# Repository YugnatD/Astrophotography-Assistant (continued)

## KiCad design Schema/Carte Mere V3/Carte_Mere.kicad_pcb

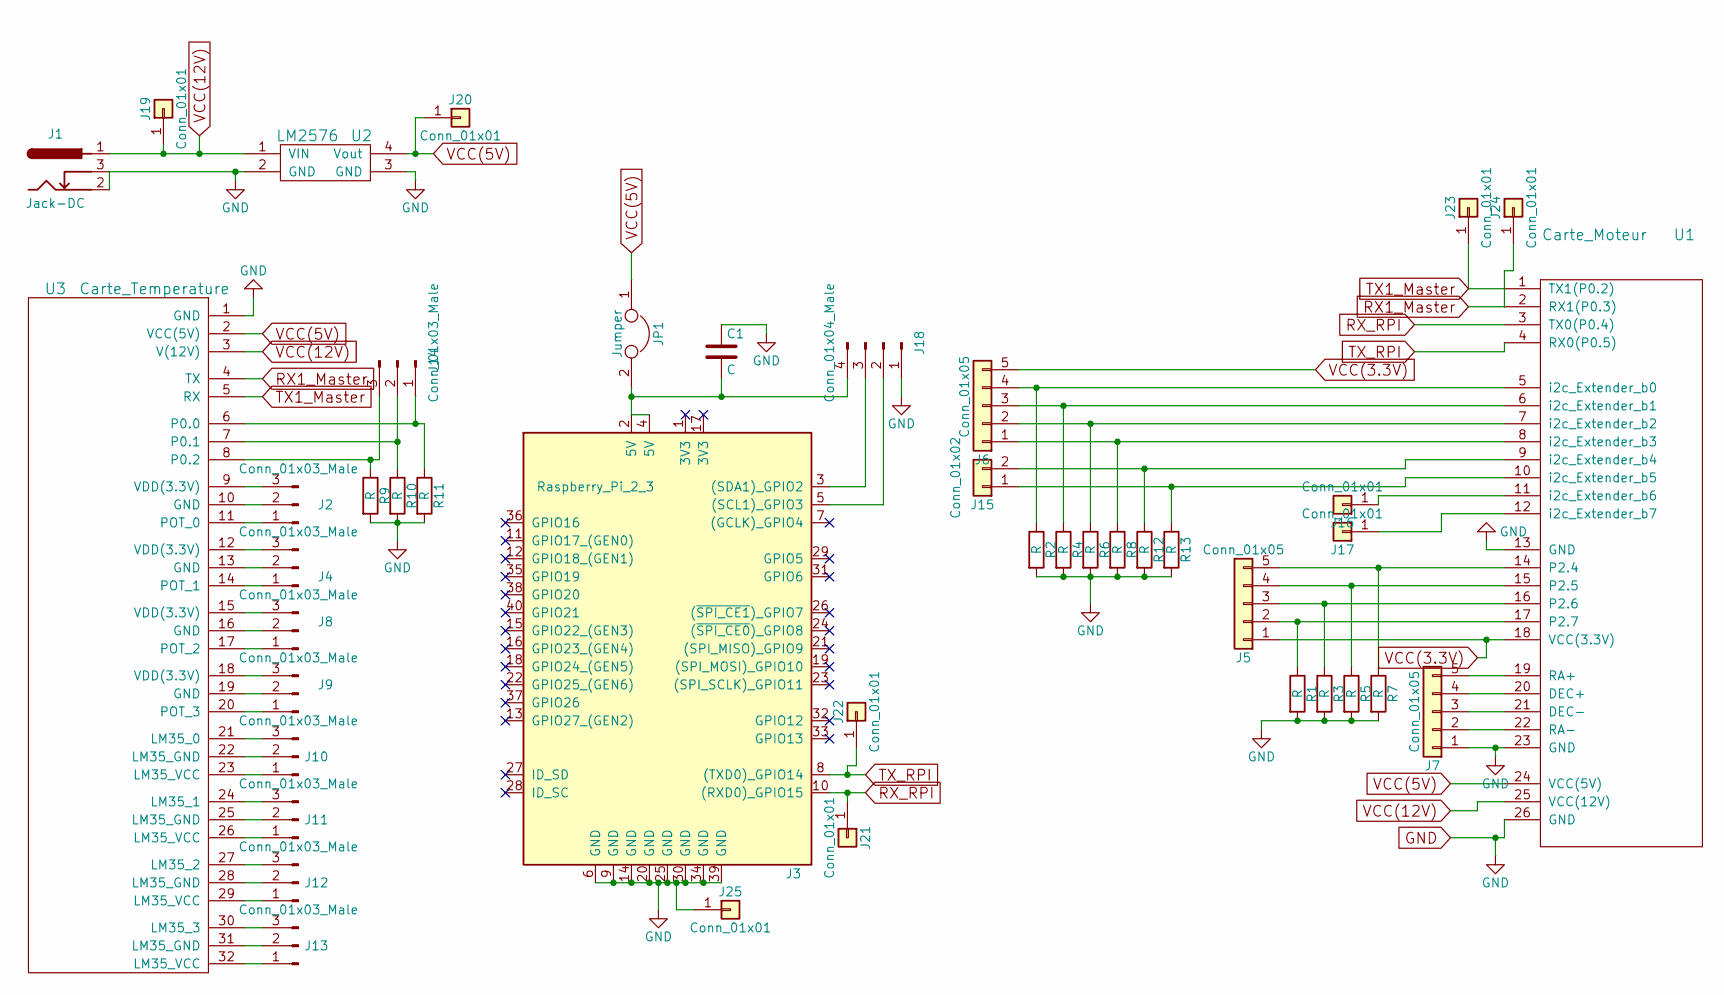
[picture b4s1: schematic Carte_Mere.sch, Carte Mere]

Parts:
C1: C; CP_Radial_D5.0mm_P2.00mm
J1: Jack-DC; JACK_ALIM
J2, J4, J8, J9, J10, J11, J12, J13, J14: Conn_01x03_Male; Pin_Header_Straight_1x03_Pitch2.54mm
J3: Raspberry_Pi_2_3; RaspberryPI3_V2
J5, J6, J7: Conn_01x05; Pin_Header_Straight_1x05_Pitch2.54mm
J15: Conn_01x02; Pin_alimentation
J16, J17, J19, J20, J21, J22, J23, J24, J25: Conn_01x01; TSC_CON1_poignard
J18: Conn_01x04_Male; Pin_Header_Straight_1x04_Pitch2.54mm
JP1: Jumper; Pin_alimentation
R1, R2, R3, R4, R5, R6, R7, R8, R9, R10, R11, R12, R13: R; R_1206_HandSoldering
U1: Carte_Moteur; Carte_Moteur_V2
U2: LM2576; Alimentation_V2
U3: Carte_Temperature

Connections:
GND: C1.1, J1.2, J1.3, J3.6 (GND), J3.9 (GND), J3.14 (GND), J3.20 (GND), J3.25 (GND), J3.30 (GND), J3.34 (GND), J3.39 (GND), J7.1, J18.1, J25.1, R1.2, R2.2, R3.2, R4.2, R5.2, R6.2, R7.2, R8.2, R9.2, R10.2, R11.2, R12.2, R13.2, U1.13 (GND), U1.23 (GND), U1.26 (GND), U2.2 (GND), U2.3 (GND), U3.1 (GND)
unnamed: C1.2, J3.2 (5V), J3.4 (5V), J18.4, JP1.2
unnamed: J2.1, U3.11 (POT_0)
unnamed: J2.2, U3.10 (GND)
unnamed: J2.3, U3.9 (VDD(3.3V))
unnamed: J4.1, U3.14 (POT_1)
unnamed: J4.2, U3.13 (GND)
unnamed: J4.3, U3.12 (VDD(3.3V))
unnamed: J5.2, R1.1, U1.17 (P2.7)
unnamed: J5.3, R3.1, U1.16 (P2.6)
unnamed: J5.4, R5.1, U1.15 (P2.5)
unnamed: J5.5, R7.1, U1.14 (P2.4)
unnamed: J6.1, R8.1, U1.8 (i2c_Extender_b3)
unnamed: J6.2, R6.1, U1.7 (i2c_Extender_b2)
unnamed: J6.3, R4.1, U1.6 (i2c_Extender_b1)
unnamed: J6.4, R2.1, U1.5 (i2c_Extender_b0)
unnamed: J7.2, U1.22 (RA-)
unnamed: J7.3, U1.21 (DEC-)
unnamed: J7.4, U1.20 (DEC+)
unnamed: J7.5, U1.19 (RA+)
unnamed: J8.1, U3.17 (POT_2)
unnamed: J8.2, U3.16 (GND)
unnamed: J8.3, U3.15 (VDD(3.3V))
unnamed: J9.1, U3.20 (POT_3)
unnamed: J9.2, U3.19 (GND)
unnamed: J9.3, U3.18 (VDD(3.3V))
unnamed: J10.1, U3.23 (LM35_VCC)
unnamed: J10.2, U3.22 (LM35_GND)
unnamed: J10.3, U3.21 (LM35_0)
unnamed: J11.1, U3.26 (LM35_VCC)
unnamed: J11.2, U3.25 (LM35_GND)
unnamed: J11.3, U3.24 (LM35_1)
unnamed: J12.1, U3.29 (LM35_VCC)
unnamed: J12.2, U3.28 (LM35_GND)
unnamed: J12.3, U3.27 (LM35_2)
unnamed: J13.1, U3.32 (LM35_VCC)
unnamed: J13.2, U3.31 (LM35_GND)
unnamed: J13.3, U3.30 (LM35_3)
unnamed: J14.1, R11.1, U3.6 (P0.0)
unnamed: J14.2, R10.1, U3.7 (P0.1)
unnamed: J14.3, R9.1, U3.8 (P0.2)
unnamed: J15.1, R13.1, U1.10 (i2c_Extender_b5)
unnamed: J15.2, R12.1, U1.9 (i2c_Extender_b4)
unnamed: J16.1, U1.11 (i2c_Extender_b6)
unnamed: J17.1, U1.12 (i2c_Extender_b7)
unnamed: J3.5 ((SCL1)_GPIO3), J18.2
unnamed: J3.3 ((SDA1)_GPIO2), J18.3
RX1_Master: J24.1, U1.2 (RX1(P0.3)), U3.4 (TX)
RX_RPI: J3.10 ((RXD0)_GPIO15), J21.1, U1.3 (TX0(P0.4))
TX1_Master: J23.1, U1.1 (TX1(P0.2)), U3.5 (RX)
TX_RPI: J3.8 ((TXD0)_GPIO14), J22.1, U1.4 (RX0(P0.5))
VCC(3.3V): J5.1, J6.5, U1.18 (VCC(3.3V))
VCC(5V): J20.1, JP1.1, U1.24 (VCC(5V)), U2.4 (Vout), U3.2 (VCC(5V))
VCC(12V): J1.1, J19.1, U1.25 (VCC(12V)), U2.1 (VIN), U3.3 (V(12V))

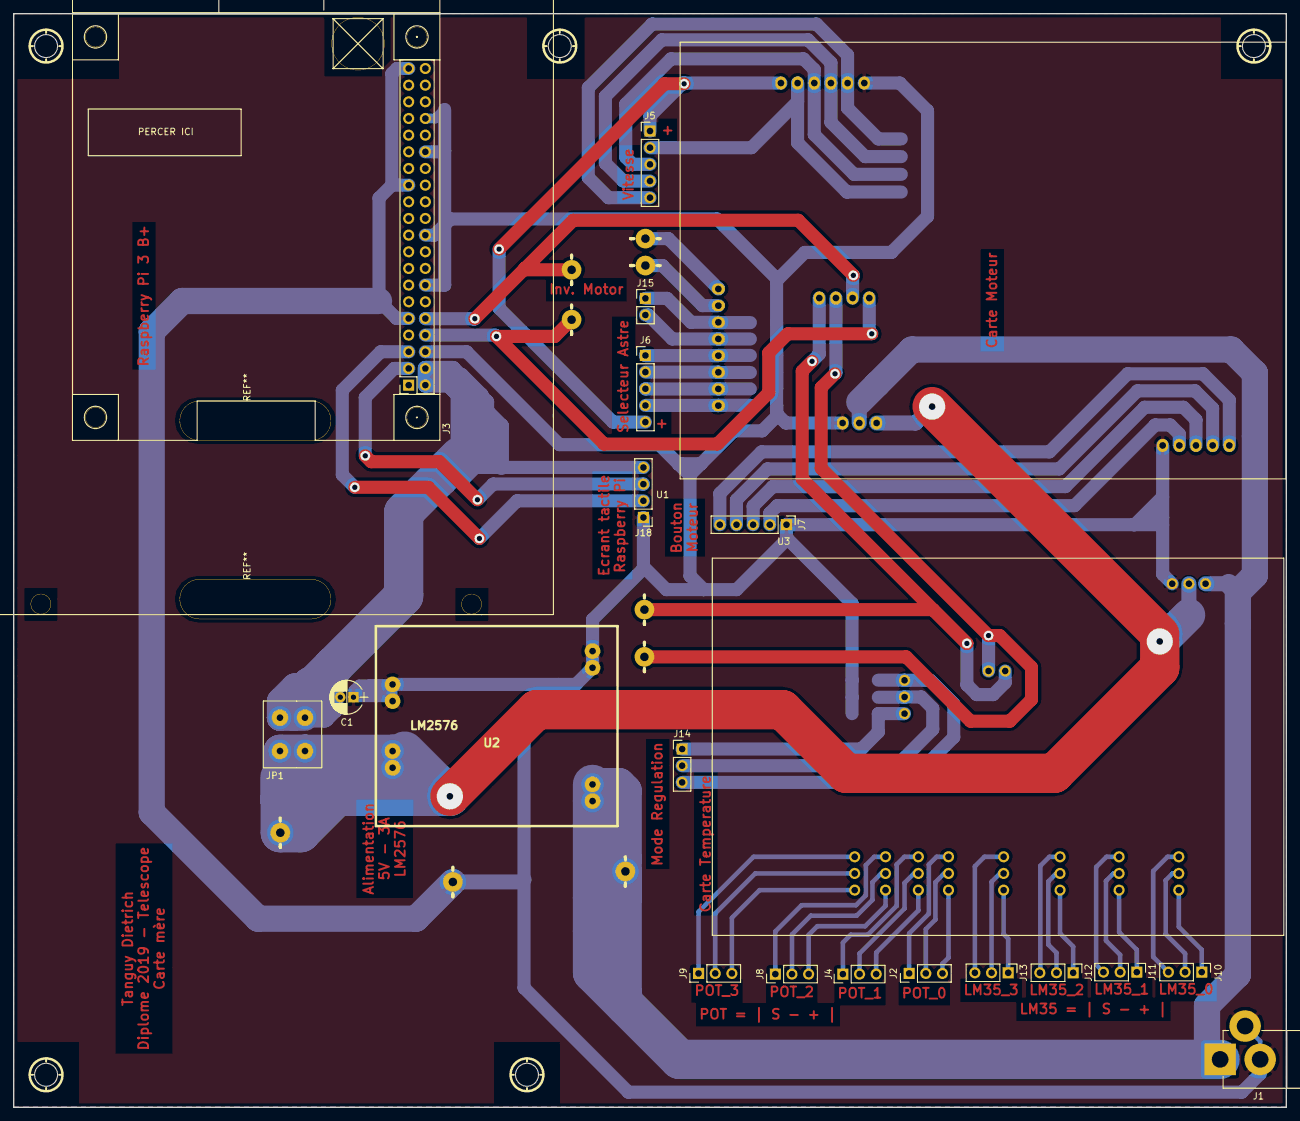
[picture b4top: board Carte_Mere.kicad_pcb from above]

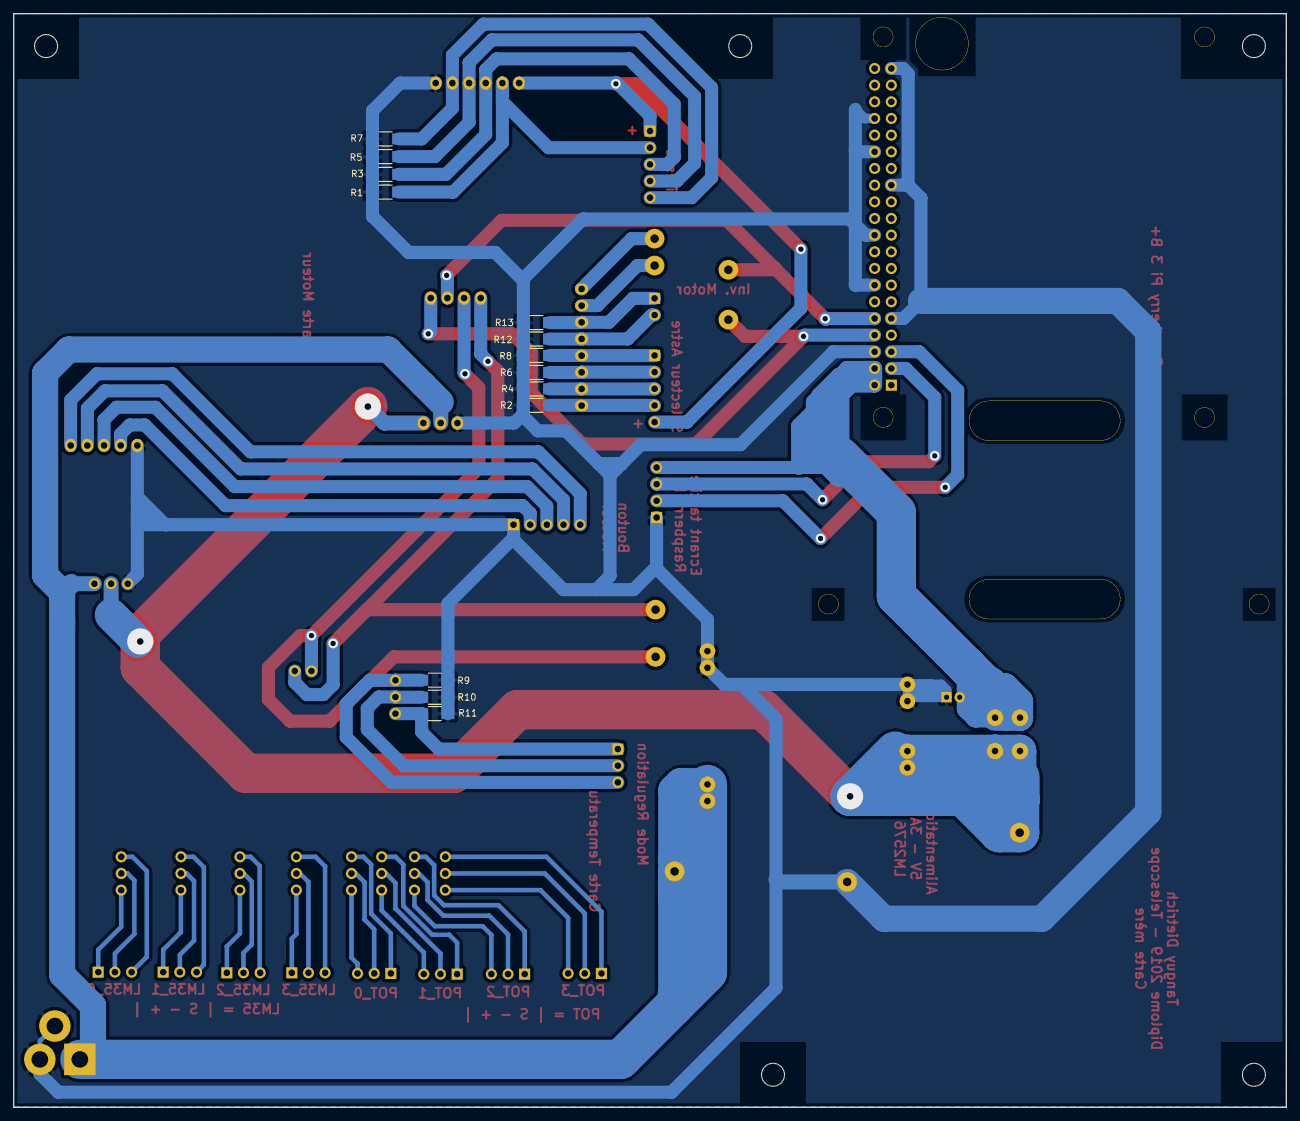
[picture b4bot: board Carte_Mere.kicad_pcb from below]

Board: 2 copper layers, 194.0 x 166.7 mm, 48 parts (15 on the bottom side), 54 nets.

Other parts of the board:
TROU_3.5, TROU_3.5#2, TROU_3.5#3, TROU_3.5#4, TROU_3.5#5: Val**; TROU_3.5

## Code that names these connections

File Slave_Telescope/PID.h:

/*===========================================================================*=
	Slave_Telescope - PID - Tanguy Dietrich
  =============================================================================
   Descriptif: 

=*===========================================================================*/

#define DEMO_CONSIGNE -200//45°C
#define CORRECTION_TEMPERATURE 50 //temperature a ajouter au dessus du point de rose

#define LM35_0_POS 0
#define LM35_0_NEG 1

#define LM35_1_POS 2
#define LM35_1_NEG 3

#define LM35_2_POS 4
#define LM35_2_NEG 5

#define LM35_3_POS 6
#define LM35_3_NEG 7

#define POT_0 8
#define POT_1 9
#define POT_2 10
#define POT_3 11



//Define Temperature
#define REF_ADC 322

#define MODE_UART 3
#define MODE_PID 2
#define MODE_POT 6

#define NMESURE 10 //nombre de mesure a faire pour une moyenne
#define DELAI_MESURE 10//temps entre chaque mesure * 50[ms]

#define KP 30
#define KI 0
#define KD 15

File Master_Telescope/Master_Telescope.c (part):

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    IE        |= 0x97;
   TR0 = 1;//lance le timer 0
   TR1=1;
   NSLEEP_RA=1;//Active le chip drv8825
   NSLEEP_DEC=0;
   DIR_RA=0;
   DIR_DEC=0;
   
   SDA=1;
   Delay_1ms (20);
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		
      if((NFAULT_RA==0)&&(NSLEEP_RA==1))//probleme sur le DRV8825 de l'axe R.A
      {
         NSLEEP_RA=0;
         Delay_1ms (10);
         NSLEEP_RA=1;
         Delay_1ms (10);//1.7ms necessaire au rallumage
      }
      
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
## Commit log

2019-11-01 Remove Old version
2020-05-18 Divers amelioration
2020-07-09 Ajout du suivi de la comete C/2020 F3 (Neowise)
2021-09-12 Ajout d'un python qui permet de faire des plate solve sur des .NEF, et divers modification
2021-09-12 deplacement du code dans un module
2021-09-12 ajout de script utile a l'utilisation du projet
2022-08-29 Working on an ascom alpaca server
2022-08-29 Working example for Connected
2022-08-29 Implemented all common method to ASCOM device
2022-08-29 Implemented get function for telescope ASCOM Alpaca
2022-08-30 Added Discovery for alpaca server
2022-08-30 ASCOM Alpaca, added get function for the telescope
2022-08-30 adding real set on set function
2022-08-31 Added configfile, and som uart communication
2022-08-31 Connection with N.I.N.A OK
2022-08-31 Bug correction : no more write with put request after async load of yaml
